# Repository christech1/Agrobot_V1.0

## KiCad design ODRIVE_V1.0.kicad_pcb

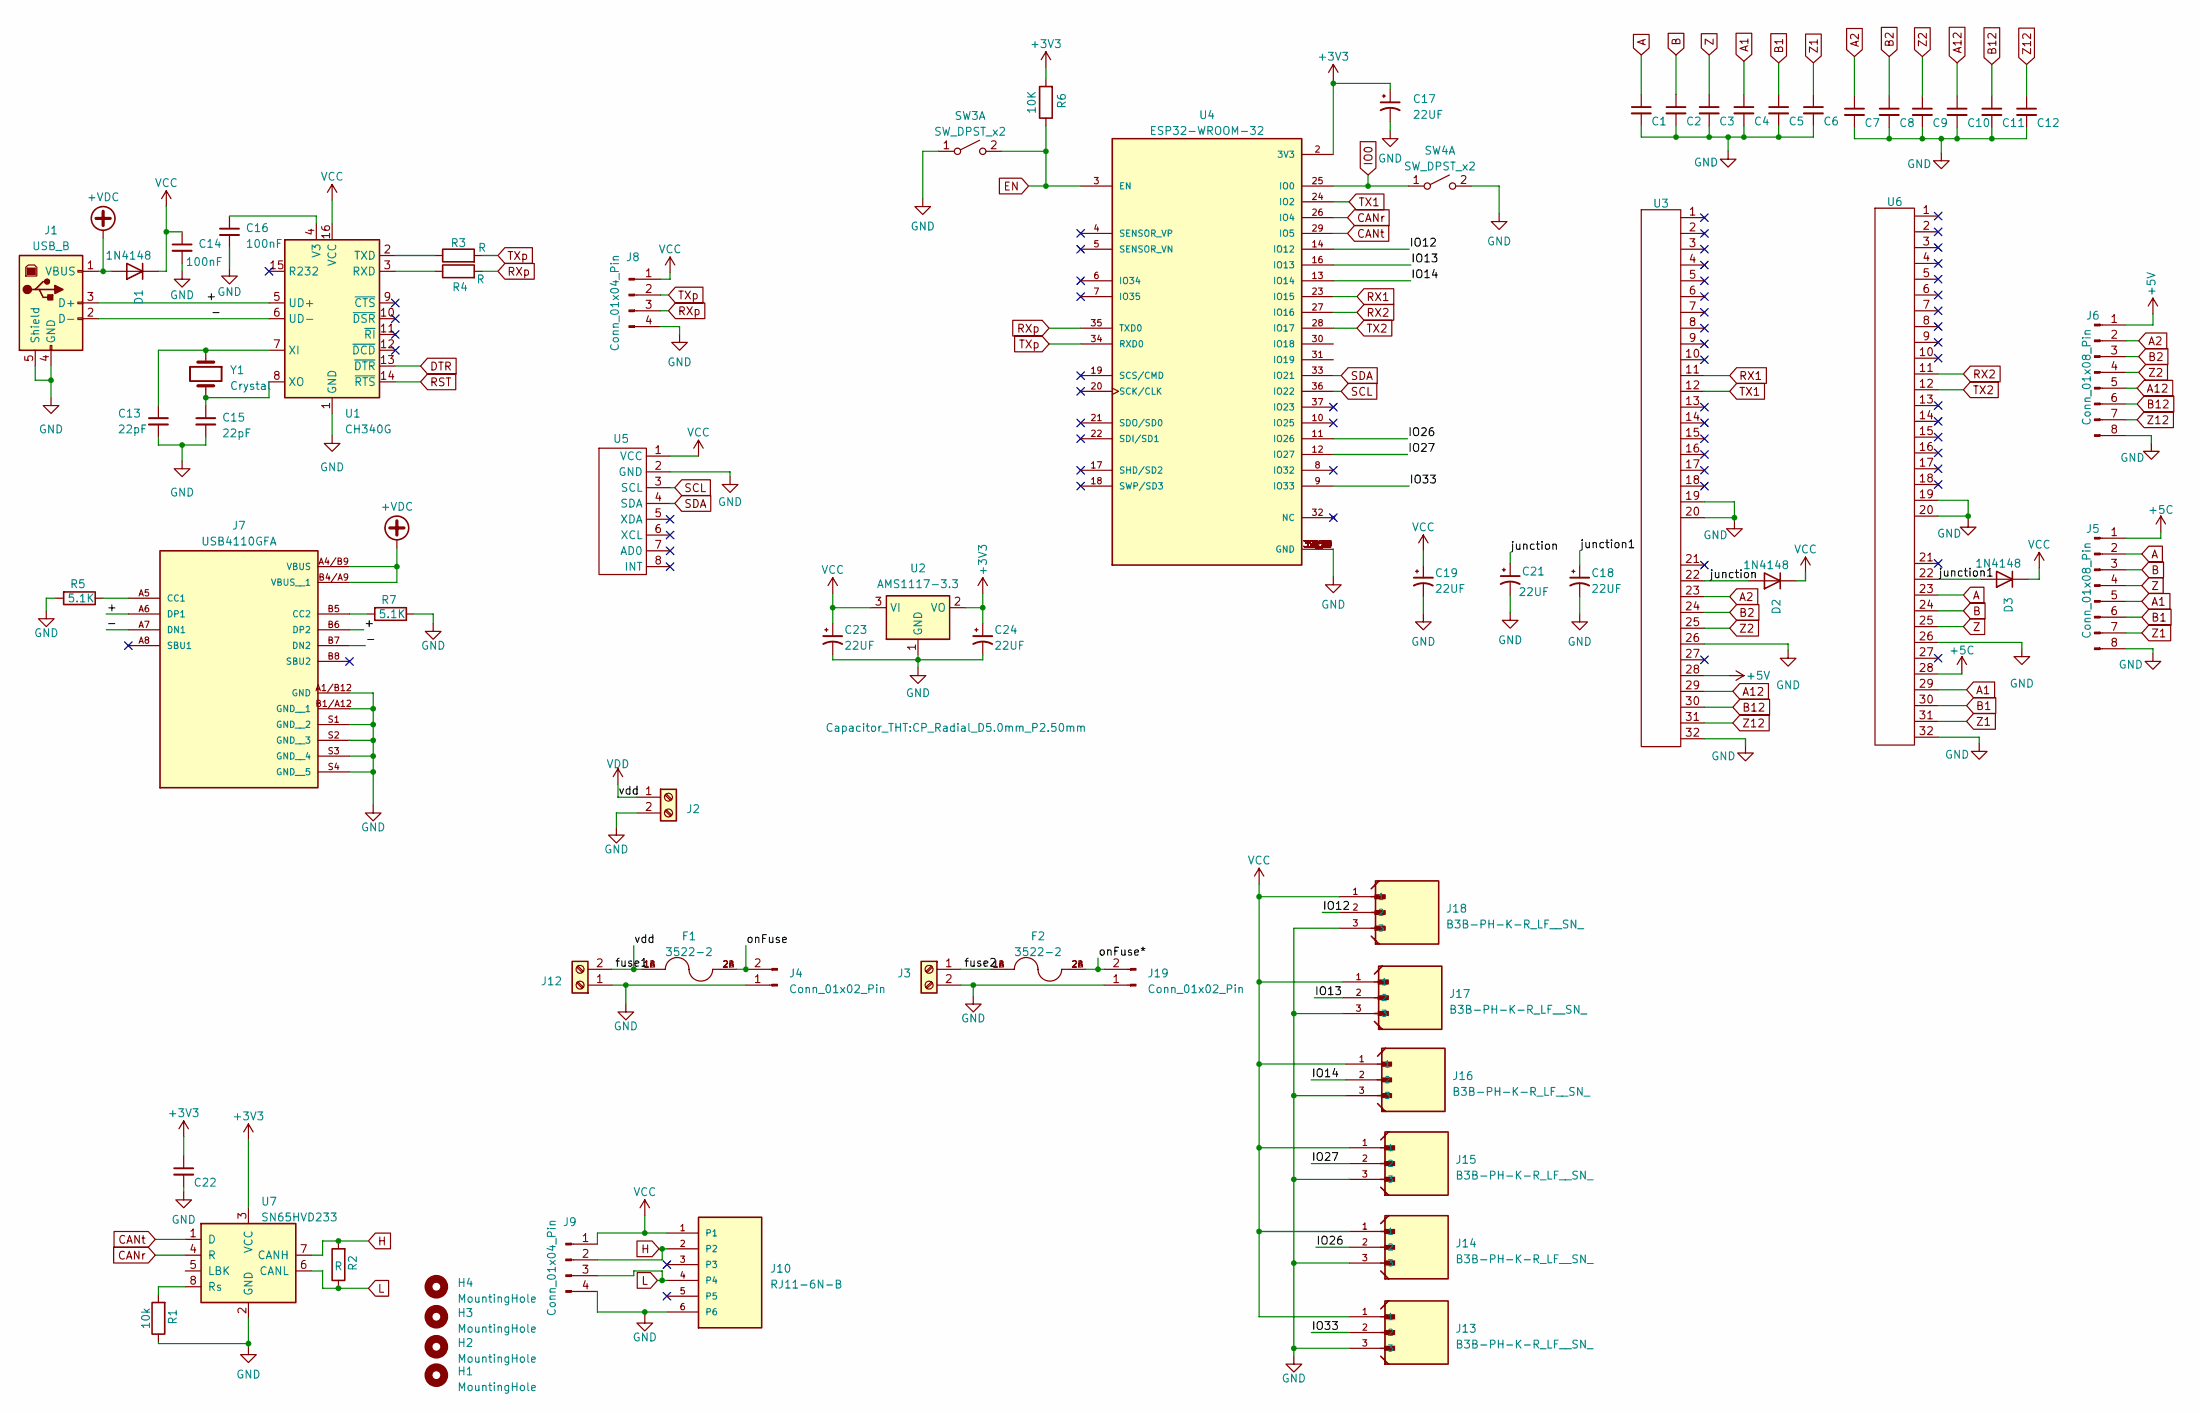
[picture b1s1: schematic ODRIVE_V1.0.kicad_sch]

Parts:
C1, C2, C3, C4, C5, C6, C7, C8, C9, C10, C11, C12, C14, C22: 100nF; C_1206_3216Metric_Pad1.33x1.80mm_HandSolder
C13, C15: 22pF; C_1206_3216Metric_Pad1.33x1.80mm_HandSolder
C16: 100nF; C_1206_3216Metric
C17, C18, C19, C21: 22UF; CP_Radial_D8.0mm_P3.50mm
C23, C24: 22UF; CP_Radial_D5.0mm_P2.50mm
D1, D2, D3: 1N4148; D_DO-35_SOD27_P7.62mm_Horizontal
F1, F2: 3522-2; FUSE_3522-2; PARTREV J
H1, H2, H3, H4: MountingHole; MountingHole_3.2mm_M3
J1: USB_B; USB_Micro-B_GCT_USB3076-30-A
J2, J3, J12: Screw_Terminal_01x02; TerminalBlock_Altech_AK300-2_P5.00mm
J4, J19: Conn_01x02_Pin; AMASS_XT30UPB-F_1x02_P5.0mm_Vertical
J5, J6: Conn_01x08_Pin; PinHeader_1x08_P2.54mm_Vertical
J7: USB4110GFA; GCT_USB4110GFA
J8, J9: Conn_01x04_Pin; PinHeader_1x04_P2.54mm_Vertical
J10: RJ11-6N-B; TE_RJ11-6N-B; PART_DESCRIPTION CONN MOD JACK 6P6C R/A UNSHLD
J13, J14, J15, J16, J17, J18: B3B-PH-K-R_LF__SN_; JST_B3B-PH-K-R_LF__SN_
R1: 10k; R_1206_3216Metric_Pad1.30x1.75mm_HandSolder
R2, R3, R4: R; R_1206_3216Metric_Pad1.30x1.75mm_HandSolder
R5, R7: 5.1K; R_1206_3216Metric_Pad1.30x1.75mm_HandSolder
R6: 10K; R_1206_3216Metric_Pad1.30x1.75mm_HandSolder
SW3, SW4: SW_DPST_x2; SW_PUSH_6mm
U1: CH340G; SOIC-16_3.9x9.9mm_P1.27mm
U2: AMS1117-3.3; SOT-223-3_TabPin2
U3, U6: Odrive_module_shield
U4: ESP32-WROOM-32; MODULE_ESP32-WROOM-32; PARTREV 2.9
U5: MPU6050_MOD
U7: SN65HVD233; SOIC-8_3.9x4.9mm_P1.27mm
Y1: Crystal; Crystal_SMD_HC49-SD_HandSoldering

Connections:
+3V3: C17.1, C22.1, C24.1, R6.2, U2.2 (VO), U4.2 (3V3), U7.3 (VCC)
+5C: J5.1, U6.28
+5V: J6.1, U3.28
+VDC: D1.2 (A), J1.1 (VBUS), J7.A4/B9 (VBUS), J7.B4/A9 (VBUS__1)
/+: J1.3 (D+), J7.A6 (DP1), J7.B6 (DP2), U1.5 (UD+)
/-: J1.2 (D-), J7.A7 (DN1), J7.B7 (DN2), U1.6 (UD-)
/IO12: J18.2, U4.14 (IO12)
/IO13: J17.2, U4.16 (IO13)
/IO14: J16.2, U4.13 (IO14)
/IO26: J14.2, U4.11 (IO26)
/IO27: J15.2, U4.12 (IO27)
/IO33: J13.2, U4.9 (IO33)
/fuse2: F2.1A, F2.1B, J3.1
/junction: C21.1, D2.2 (A), U3.22
/junction1: C18.1, D3.2 (A), U6.22
/onFuse: F1.2A, F1.2B, J4.2
/onFuse*: F2.2A, F2.2B, J19.2
A: C1.1, J5.2, U6.23
A1: C4.1, J5.5, U6.29
A2: C7.1, J6.2, U3.23
A12: C10.1, J6.5, U3.29
B: C2.1, J5.3, U6.24
B1: C5.1, J5.6, U6.30
B2: C8.1, J6.3, U3.24
B12: C11.1, J6.6, U3.30
CANr: U4.26 (IO4), U7.4 (R)
CANt: U4.29 (IO5), U7.1 (D)
DTR: U1.13 (~DTR)
EN: R6.1, SW3.2 (B), U4.3 (EN)
GND: C1.2, C2.2, C3.2, C4.2, C5.2, C6.2, C7.2, C8.2, C9.2, C10.2, C11.2, C12.2, C13.2, C14.2, C15.2, C16.2, C17.2, C18.2, C19.2, C21.2, C22.2, C23.2, C24.2, J1.4 (GND), J1.5 (Shield), J2.2, J3.2, J4.1, J5.8, J6.8, J7.A1/B12 (GND), J7.B1/A12 (GND__1), J7.S1 (GND__2), J7.S2 (GND__3), J7.S3 (GND__4), J7.S4 (GND__5), J8.4, J9.4, J10.6, J12.1, J13.3, J14.3, J15.3, J16.3, J17.3, J18.3, J19.1, R1.1, R5.2, R7.1, SW3.1 (A), SW4.2 (B), U1.1 (GND), U2.1 (GND), U3.19, U3.20, U3.26, U3.32, U4.1 (GND), U4.15 (GND), U4.38 (GND), U4.39_1 (GND), U4.39_2 (GND), U4.39_3 (GND), U4.39_4 (GND), U4.39_5 (GND), U4.39_6 (GND), U4.39_7 (GND), U4.39_8 (GND), U4.39_9 (GND), U4.39_10 (GND), U4.39_11 (GND), U4.39_12 (GND), U4.39_13 (GND), U4.39_14 (GND), U4.39_15 (GND), U4.39_16 (GND), U4.39_17 (GND), U4.39_18 (GND), U4.39_19 (GND), U4.39_20 (GND), U4.39_21 (GND), U5.2 (GND), U6.19, U6.20, U6.26, U6.32, U7.2 (GND)
H: J9.2, J10.2, R2.2, U7.7 (CANH)
IO0: SW4.1 (A), U4.25 (IO0)
L: J9.3, J10.4, R2.1, U7.6 (CANL)
unnamed: J7.A5 (CC1), R5.1
unnamed: J7.B5 (CC2), R7.2
unnamed: R4.1, U1.3 (RXD)
unnamed: R3.1, U1.2 (TXD)
unnamed: C16.1, U1.4 (V3)
unnamed: C13.1, U1.7 (XI), Y1.1
unnamed: C15.1, U1.8 (XO), Y1.2
unnamed: R1.2, U7.8 (Rs)
RST: U1.14 (~RTS)
RX1: U3.11, U4.23 (IO15)
RX2: U4.27 (IO16), U6.11
RXp: J8.3, R4.2, U4.35 (TXD0)
SCL: U4.36 (IO22), U5.3 (SCL)
SDA: U4.33 (IO21), U5.4 (SDA)
TX1: U3.12, U4.24 (IO2)
TX2: U4.28 (IO17), U6.12
TXp: J8.2, R3.2, U4.34 (RXD0)
VCC: C14.1, C19.1, C23.1, D1.1 (K), D2.1 (K), D3.1 (K), J8.1, J9.1, J10.1, J13.1, J14.1, J15.1, J16.1, J17.1, J18.1, U1.16 (VCC), U2.3 (VI), U5.1 (VCC)
VDD: F1.1A, F1.1B, J2.1, J12.2
Z: C3.1, J5.4, U6.25
Z1: C6.1, J5.7, U6.31
Z2: C9.1, J6.4, U3.25
Z12: C12.1, J6.7, U3.31

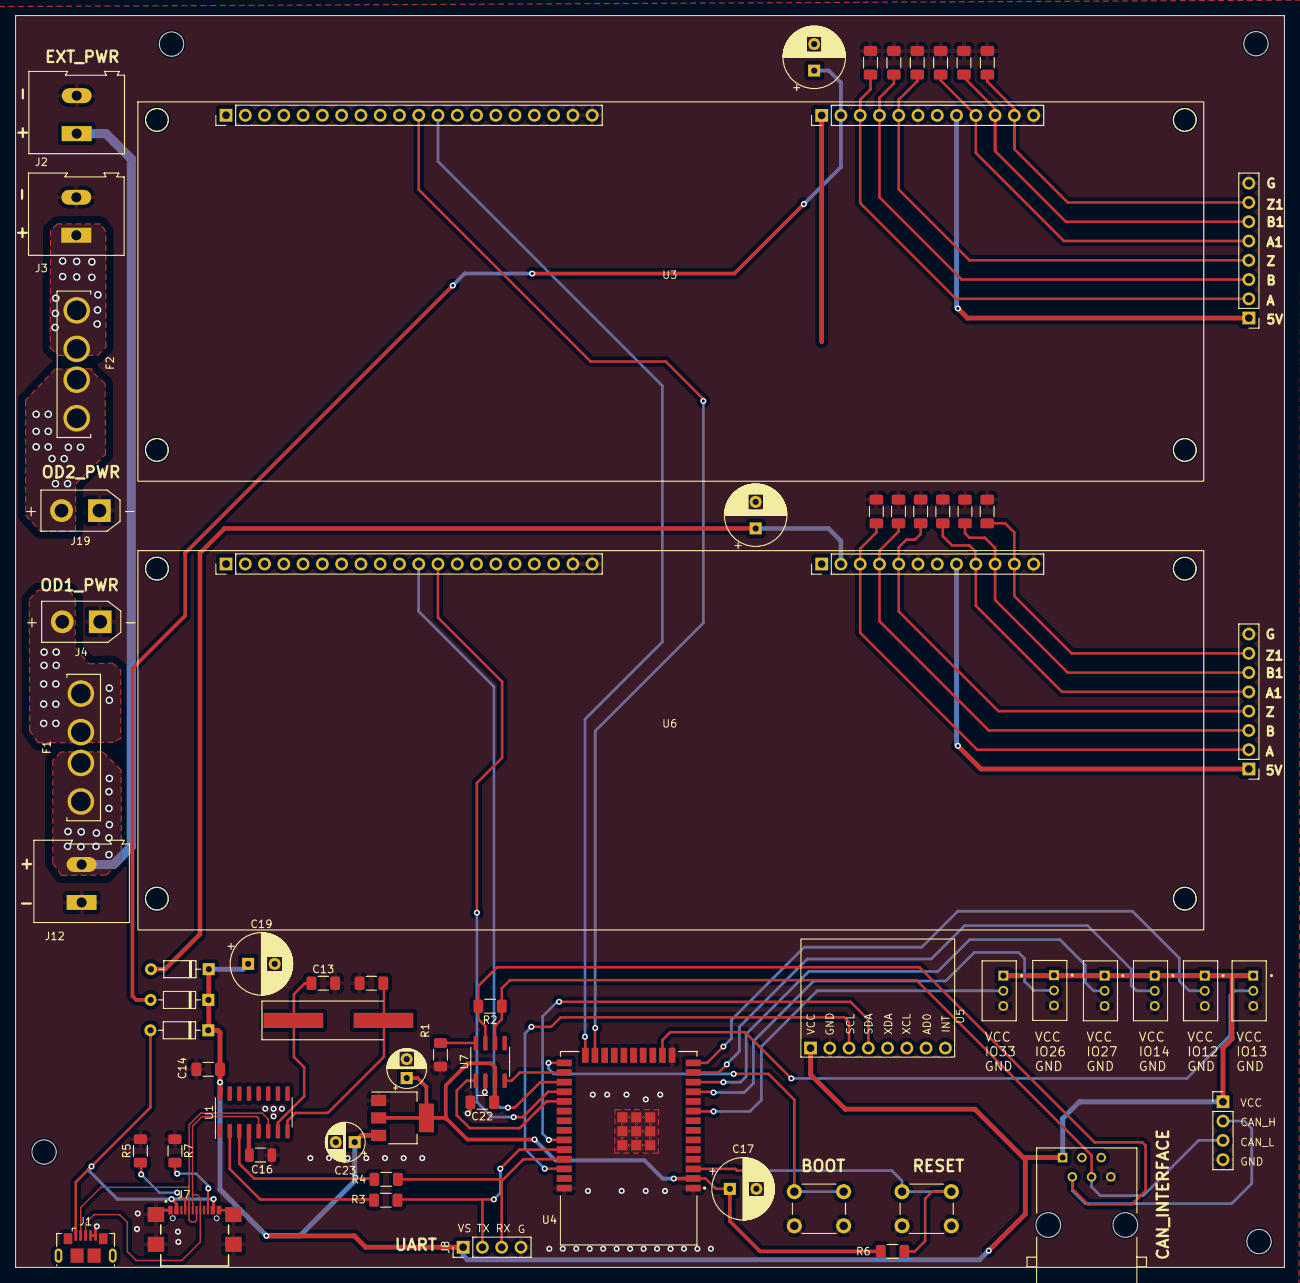
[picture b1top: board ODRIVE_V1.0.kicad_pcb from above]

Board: 2 copper layers, 167.3 x 165.0 mm, 67 parts (0 on the bottom side), 54 nets.

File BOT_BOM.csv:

Item,Qty,Reference(s),Value,qty/price,total price,price/pcs by vendor,,,,,,,,,,
1,13,"C1, C2, C3, C4, C5, C6, C7, C8, C9, C10, C11, C12, C22",100n,,"RWF 1,000",,,,,,,,,,,
2,2,"C13, C15",22pF,,RWF 500,,,,,,,,,,,
3,1,C14,100nF,,RWF 300,,,,,,,,,,,
4,1,C16,100nF,,RWF 300,,,,,,,,,,,
5,3,"C17, C18, C21",22UF,,"RWF 1,000",,,,,,,,,,,
6,2,"C23, C24",22UF,,"RWF 1,000",,,,,,,,,,,
7,3,"D1, D2, D3",1N4148,,RWF 500,,,,,,,,,,,
8,2,"F1, F2",3522-2,,"RWF 3,000",,,,,,,,,,,
9,1,J1,USB_B,,"RWF 1,000",,,,,,,,,,,
10,4,"J2, J3, J11, J12",Screw_Terminal_01x02,,"RWF 2,000",,,,,,,,,,,
11,1,J4,Conn_01x02_Pin,,RWF 300,,,,,,,,,,,
12,2,"J5, J6",Conn_01x08_Pin,,RWF 600,,,,,,,,,,,
13,1,J7,USB4110GFA,,"RWF 1,000",,,,,,,,,,,
14,1,J8,Conn_01x04_Pin,,RWF 100,,,,,,,,,,,
15,1,J10,RJ11-6N-B,,RWF 500,,,,,,,,,,,
16,1,R1,10k,,RWF 100,,,,,,,,,,,
17,3,"R2, R3, R4",R,,RWF 300,,,,,,,,,,,
18,2,"R5, R7",5.1K,,RWF 200,,,,,,,,,,,
19,1,R6,10K,,RWF 100,,,,,,,,,,,
20,2,"SW3, SW4",SW_DPST_x2,,RWF 400,,,,,,,,,,,
21,1,U1,CH340G,,"RWF 3,000",,,,,,,,,,,
22,1,U2,AMS1117-3.3,,"RWF 1,000",,,,,,,,,,,
23,2,"U3, U6",~,,,,,,,,,,,,,
24,1,U4,ESP32-WROOM-32,,"RWF 2,000",,,,,,,,,,,
25,1,U5,~,,"RWF 3,000",,,,,,,,,,,
26,13,"C1, C2, C3, C4, C5, C6, C7, C8, C9, C10, C11, C12, C23",100n,,"RWF 1,500",,,,,,,,,,,
,,,,,"RWF 24,700",,,,,,,,,,,

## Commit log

2024-06-08 agrobot 1st psh
2024-06-15 updating to finals
2024-06-17 updating finals ltst
2024-06-25 addingg
